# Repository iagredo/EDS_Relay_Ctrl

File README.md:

# EDS_Relay_Ctrl
Modulo de control para reles tipo Latch

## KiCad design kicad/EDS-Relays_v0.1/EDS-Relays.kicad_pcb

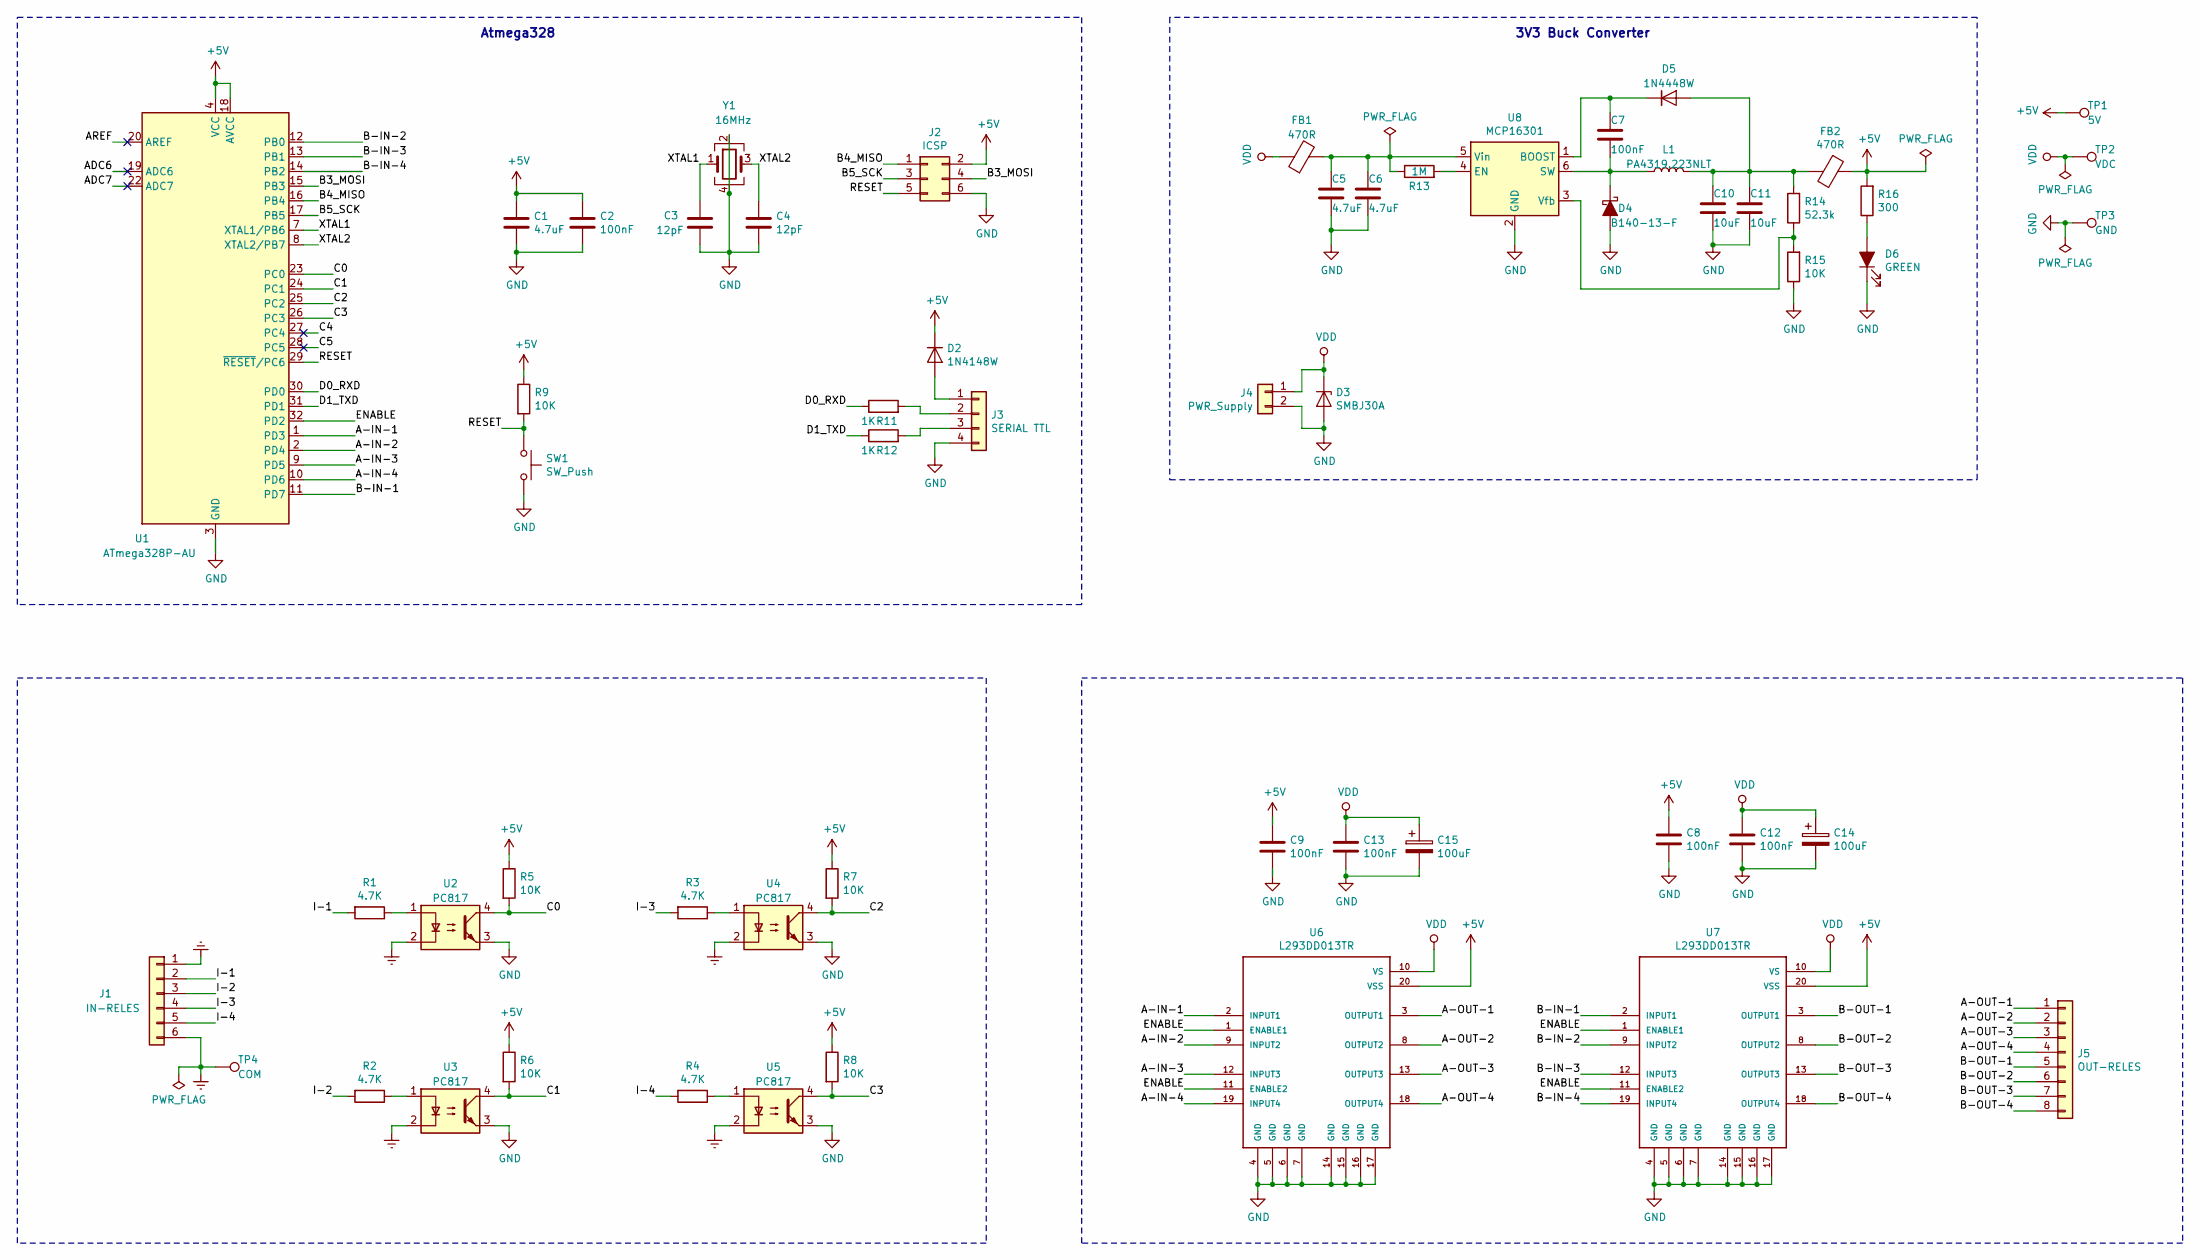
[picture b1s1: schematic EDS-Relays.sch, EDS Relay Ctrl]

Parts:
C1, C5, C6: 4.7uF; C_1206
C2, C7, C8, C9, C12, C13: 100nF; C_0603
C3, C4: 12pF; C_0603
C10, C11: 10uF; C_0805
C14, C15: 100uF; CP_Elec_6.3x7.7
D2: 1N4148W; D_SOD-123
D3: SMBJ30A; D_SMB
D4: B140-13-F; D_SMA
D5: 1N4448W; D_SOD-123
D6: GREEN; LED_0603
FB1, FB2: 470R; L_0603
J1: IN-RELES; BOR-6POS-691313510006
J2: ICSP; Pin_Header_Straight_2x03_Pitch2.54mm
J3: SERIAL TTL; Pin_Header_Straight_1x04_Pitch2.54mm
J4: PWR_Supply; BOR-2POS-PHOENIX_1757242
J5: OUT-RELES; BOR-8POS_1
L1: PA4319.223NLT; PA4319
R1, R2, R3, R4: 4.7K; R_1206_HandSoldering
R5, R6, R7, R8, R9, R15: 10K; R_0603
R11, R12: 1K; R_0603
R13: 1M; R_0402
R14: 52.3k; R_0603
R16: 300; R_0402
SW1: SW_Push; SW_SPST_B3S-1000
TP1: 5V; Measurement_Point_Round-SMD-Pad_Small
TP2: VDC; Measurement_Point_Round-SMD-Pad_Small
TP3: GND; Measurement_Point_Round-SMD-Pad_Small
TP4: COM; Measurement_Point_Round-SMD-Pad_Small
U1: ATmega328P-AU; TQFP-32_7x7mm_Pitch0.8mm
U2, U3, U4, U5: PC817; DIP-4_W9.53mm_SMD
U6, U7: L293DD013TR; SOIC-20W_7.5x12.8mm_Pitch1.27mm
U8: MCP16301; SOT-23-6
Y1: 16MHz; Crystal_SMD_3225-4pin_3.2x2.5mm

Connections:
+5V: C1.1, C2.1, C8.1, C9.1, D2.1 (K), FB2.1, J2.2, R5.1, R6.1, R7.1, R8.1, R9.1, R16.2, TP1.1, U1.4 (VCC), U1.6 (VCC), U1.18 (AVCC), U6.20 (VSS), U7.20 (VSS)
/A-IN-1: U1.1 (PD3), U6.2 (INPUT1)
/A-IN-2: U1.2 (PD4), U6.9 (INPUT2)
/A-IN-3: U1.9 (PD5), U6.12 (INPUT3)
/A-IN-4: U1.10 (PD6), U6.19 (INPUT4)
/A-OUT-1: J5.1, U6.3 (OUTPUT1)
/A-OUT-2: J5.2, U6.8 (OUTPUT2)
/A-OUT-3: J5.3, U6.13 (OUTPUT3)
/A-OUT-4: J5.4, U6.18 (OUTPUT4)
/ADC6: U1.19 (ADC6)
/ADC7: U1.22 (ADC7)
/AREF: U1.20 (AREF)
/B3_MOSI: J2.4, U1.15 (PB3)
/B4_MISO: J2.1, U1.16 (PB4)
/B5_SCK: J2.3, U1.17 (PB5)
/B-IN-1: U1.11 (PD7), U7.2 (INPUT1)
/B-IN-2: U1.12 (PB0), U7.9 (INPUT2)
/B-IN-3: U1.13 (PB1), U7.12 (INPUT3)
/B-IN-4: U1.14 (PB2), U7.19 (INPUT4)
/B-OUT-1: J5.5, U7.3 (OUTPUT1)
/B-OUT-2: J5.6, U7.8 (OUTPUT2)
/B-OUT-3: J5.7, U7.13 (OUTPUT3)
/B-OUT-4: J5.8, U7.18 (OUTPUT4)
/C0: R5.2, U1.23 (PC0), U2.4
/C1: R6.2, U1.24 (PC1), U3.4
/C2: R7.2, U1.25 (PC2), U4.4
/C3: R8.2, U1.26 (PC3), U5.4
/C4: U1.27 (PC4)
/C5: U1.28 (PC5)
/D0_RXD: R11.1, U1.30 (PD0)
/D1_TXD: R12.1, U1.31 (PD1)
/ENABLE: U1.32 (PD2), U6.1 (ENABLE1), U6.11 (ENABLE2), U7.1 (ENABLE1), U7.11 (ENABLE2)
/I-1: J1.2, R1.2
/I-2: J1.3, R2.2
/I-3: J1.4, R3.2
/I-4: J1.5, R4.2
/RESET: J2.5, R9.2, SW1.1, U1.29 (~RESET~/PC6)
/XTAL1: C3.1, U1.7 (XTAL1/PB6), Y1.1
/XTAL2: C4.1, U1.8 (XTAL2/PB7), Y1.3
Earth: J1.1, J1.6, TP4.1, U2.2, U3.2, U4.2, U5.2
GND: C1.2, C2.2, C3.2, C4.2, C5.2, C6.2, C8.2, C9.2, C10.2, C11.2, C12.2, C13.2, C14.2, C15.2, D3.2 (A), D4.2 (A), D6.1 (K), J2.6, J3.4, J4.2, R15.1, SW1.2, TP3.1, U1.3 (GND), U1.5 (GND), U1.21 (GND), U2.3, U3.3, U4.3, U5.3, U6.4 (GND), U6.5 (GND), U6.6 (GND), U6.7 (GND), U6.14 (GND), U6.15 (GND), U6.16 (GND), U6.17 (GND), U7.4 (GND), U7.5 (GND), U7.6 (GND), U7.7 (GND), U7.14 (GND), U7.15 (GND), U7.16 (GND), U7.17 (GND), U8.2 (GND), Y1.2, Y1.4
unnamed: C5.1, C6.1, FB1.2, R13.1, U8.5 (Vin)
unnamed: C7.1, D5.1 (K), U8.1 (BOOST)
unnamed: C7.2, D4.1 (K), L1.1, U8.6 (SW)
unnamed: C10.1, C11.1, D5.2 (A), FB2.2, L1.2, R14.2
unnamed: D2.2 (A), J3.1
unnamed: D6.2 (A), R16.1
unnamed: J3.2, R11.2
unnamed: J3.3, R12.2
unnamed: R1.1, U2.1
unnamed: R2.1, U3.1
unnamed: R3.1, U4.1
unnamed: R4.1, U5.1
unnamed: R13.2, U8.4 (EN)
unnamed: R14.1, R15.2, U8.3 (Vfb)
VDD: C12.1, C13.1, C14.1, C15.1, D3.1 (K), FB1.1, J4.1, TP2.1, U6.10 (VS), U7.10 (VS)

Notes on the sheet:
3V3 Buck Converter
Atmega328

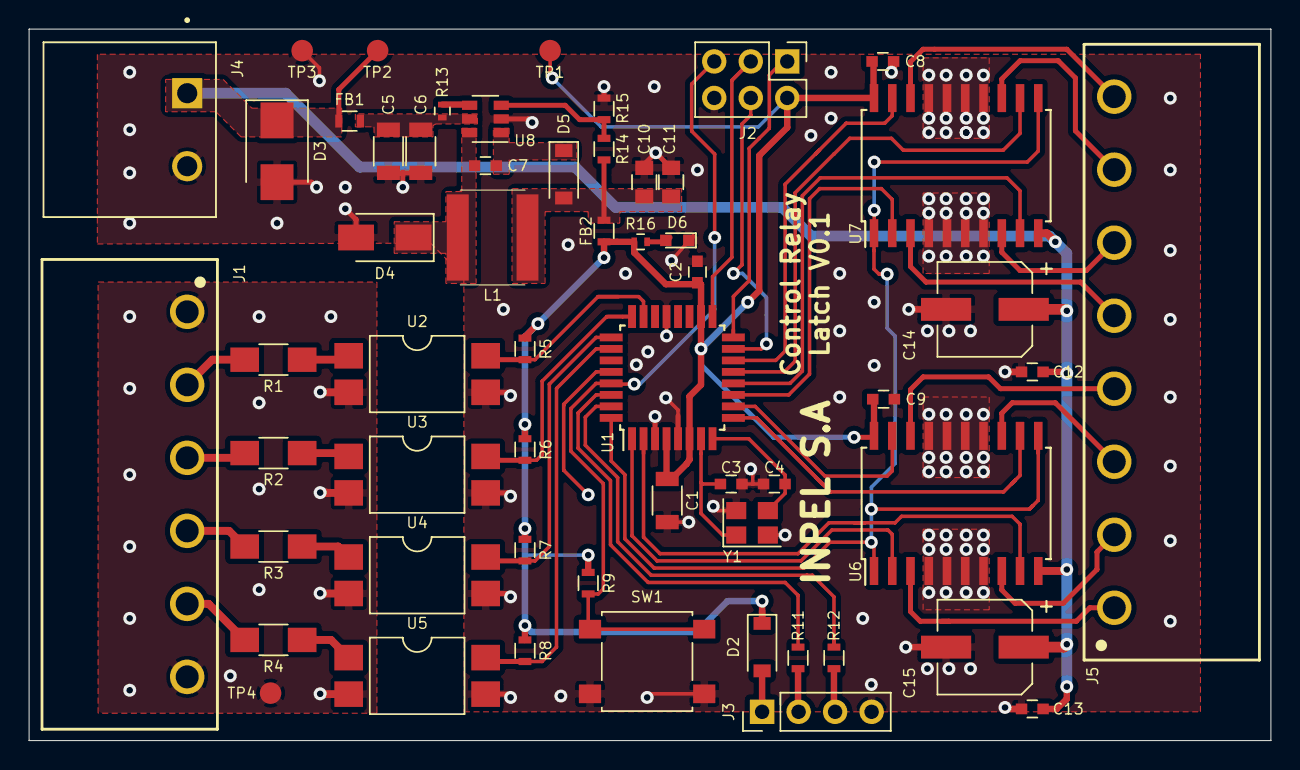
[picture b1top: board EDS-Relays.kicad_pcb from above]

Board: 2 copper layers, 86.4 x 49.5 mm, 57 parts (0 on the bottom side), 51 nets.

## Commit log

2020-11-03 Version 01 FW funcional, HW funcional, carcasa incompatible con borneras PLUG - test funcional aprobado
